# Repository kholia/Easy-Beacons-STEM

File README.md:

### Easy Beacons

A simple and easy Raspberry Pi Pico powered WSPR, and FT8 beacon system which
uses GPS for timing.

Note: The whole project can be assembled on a breadboard (including the [~100mW
amplifier](./QRPp-Amplifier-v2)) in under an hour - do give it a go!

The whole design is modular, parametric (cost and others), field repairable,
and super extensible. It is almost trivial to add support for more `beacon
modes`.

Note: This documentation is a WIP (work-in-progress), and can't be trusted
100%. Please switch on your brain, and read the actual code and schematics.
This repository has more than 10 sub-projects, and can get confusing to follow
unless you read the actual code, and schematics.

#### Build Steps

Use a stable version of the Arduino IDE 1.8.19 or later to build the project.

If you are on Linux, execute the following steps:

```
sudo apt-get install git  # install 'git' if needed

git clone https://github.com/kholia/Easy-Beacons-STEM.git

make install_arduino_cli
make install_platform
make deps
```

If you are using Windows OS, execute the following steps:

- Download this repository.

- Extract the downloaded zip file to a folder.

- Run the `setup_arduino_ide.bat` file inside this folder.

Note: Change the following lines in the code to use your values:

```
char message[] = "VU3CER VU3FOE MK68";
char call[] = "VU3FOE";
char loc[] = "MK68";
uint8_t dbm = 27;
```

#### Amplified-WSPR-Beacon-v3

- Power from a USB power bank @ 5v.

Note: The PCB version of the `Amplified-WSPR-Beacon-v3` sub-project uses the
`Pico-Beacons-GPS-v2` firmware (code).

#### Amplified-WSPR-Beacon

- Do NOT power with more than 8.4v!

- Use an 7.5v AC adapter for continuous use

Note: The PCB version of the `Amplified-WSPR-Beacon` sub-project uses the `Pico-Beacons-GPS-v2` firmware (code).

Note 2: The `Amplified-WSPR-Beacon-v2` project uses 5v from USB.

#### Usage

When `SW1` switch is OFF, the system acts as a WSPR beacon.

When `SW1` switch is ON, the system acts as a FT8 beacon.

TIP: Please use a local (or nearby) receiver to receive and decode the beacon
signals! This is important to ensure that your beacon is TX'ing correctly.

#### Schematic

Here is the schematic for the `Pico-Beacons` sketch:

Pin 16 (GP16) is SDA and Pin 17 (GP17) is SCL - connect Si5351 module to these
pins. Connect GPS's TX pin to pin 12 (GP9) of Pi Pico.

#### Performance

7W (or less) of HF RF power offers global communications coverage when
propagation is good:

WSPR mode demo:

#### Battery System Recommendation

I recommend using a LiFePo4 (LFP) battery which has good energy density and is
also priced decently well.

Use the LFP battery with a `1S LFP BMS`.

The BMS' output can be connected directly to the 3.3v input of the ESP8266
module.

https://www.waveshare.com/wiki/Solar_Power_Manager - this `Solar Power
Management Module, for 6V~24V Solar Panel` works pretty well.

#### Power Notes

This will need a HF RF PA in many cases to be usable on the air.

You can also start with the easy-to-build and breadboard-friendly [QRPp-Amplifier-v2](./QRPp-Amplifier-v2).

#### Safety Notes

- Connect a 1k or 2.2k resistor between Si5351 CLK outputs and GND.

- Connect a series 100nF at Si5351 CLK outputs.

- Do NOT connect a LED to the output(s) of Si5351 directly. Use a 330 or 470
  ohm resistor in series or use a transistor driver at the Si5351 outputs
  (better).

#### Compliance Notes

Please use a LPF at the output.

#### Gotchas

- https://github.com/mikalhart/TinyGPSPlus/issues/30 (NEO-6M modules can be buggy)

#### BOM

- 1 x 3/5mm LED (purple or pink is recommended)

- 1 x small regular (spst) chassis mount switch

- 1 x 0.25w 470 ohm resistor (CFR / MFR)

- High quality dupont cables / jumper cables

- Couple of 100nF 50V MLCC

- Zero PCB of a suitable size

- Raspberry Pi Pico board

- GPS module - NEO-7-M or better

- BS170 MOSFET (original only)

- SN74ACT00N (DIP 14 NAND Logic IC)

- Si5351A Module

#### Install the firmware on Pi Pico

- Hold down the BOOTSEL button on your Pico (keep holding it down) and plug it
  into your computer's USB port.

  Now release the BOOTSEL button.

- Open Explorer, and open the RPI-RP2 directory like you would any other hard
  drive.

- Drag and drop the UF2 file (`firmware.uf2`) from this folder into the RPI-RP2
  directory.

- Done ;)

#### Build from source

Use the latest Arduino IDE along with https://github.com/earlephilhower/arduino-pico
to build this source code.

#### Next Steps

Check out the ADX and PDX radio designs for added fun!

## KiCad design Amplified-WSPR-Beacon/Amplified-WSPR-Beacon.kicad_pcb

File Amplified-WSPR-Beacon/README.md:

Output with 7.4v @ drain is around 400mW @ 28 MHz. Not too bad - twice that of
the `Intl. WSPR Beacon` device.

This project is also called the `Rogue Radio - v1` ;)

Cost: < 1800 INR (not including the 2s 18650 battery pack) which is around 22
USD.

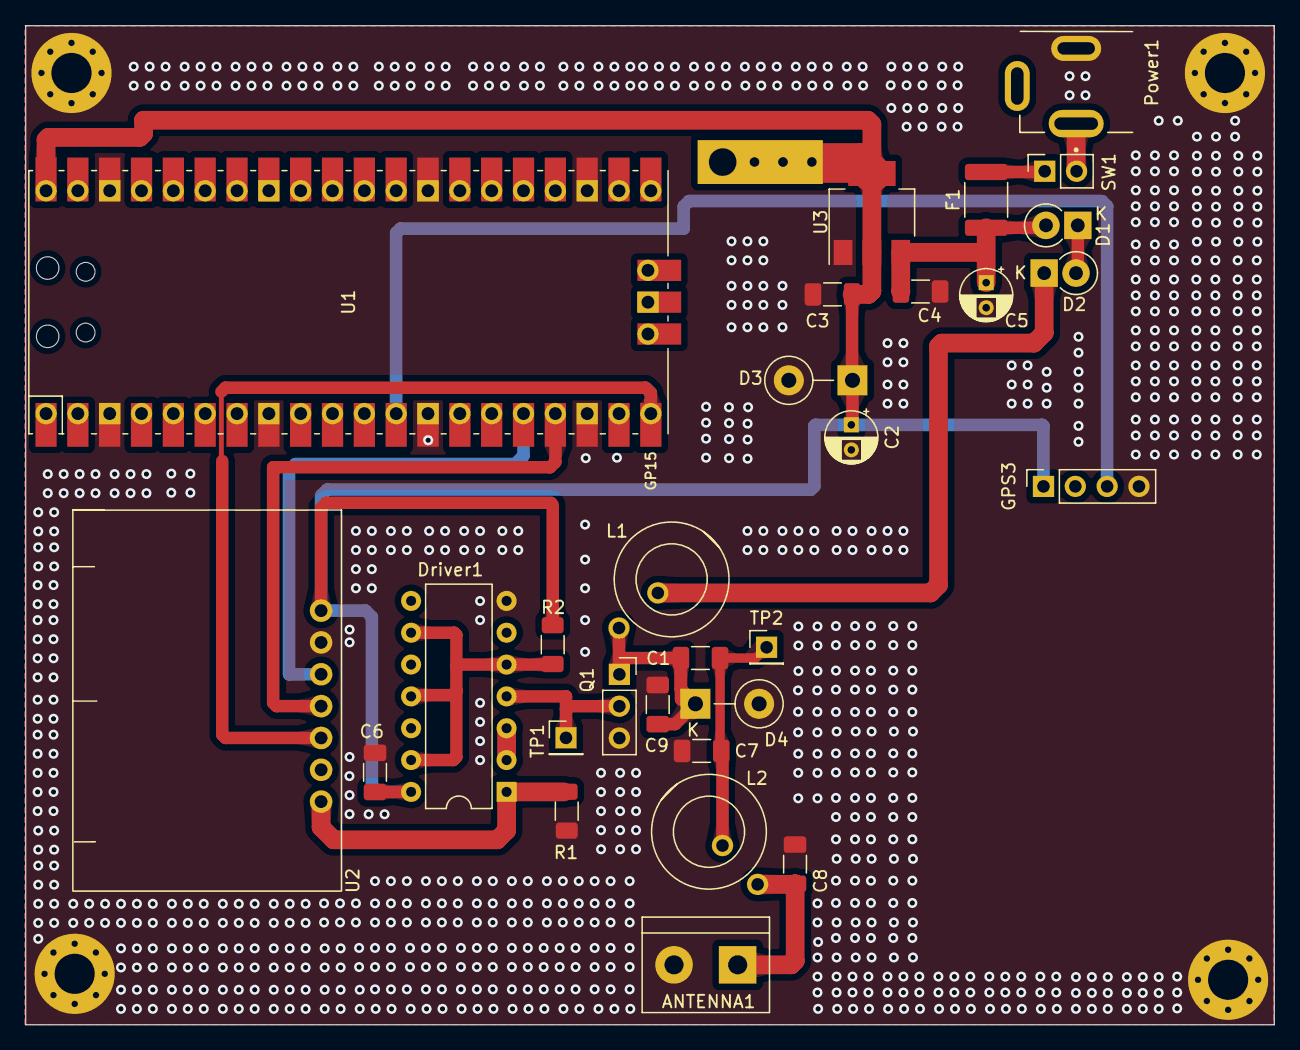
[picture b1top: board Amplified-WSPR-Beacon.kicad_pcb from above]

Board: 2 copper layers, 99.6 x 79.7 mm, 34 parts (0 on the bottom side), 18 nets.

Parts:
ANTENNA1: Screw_Terminal_01x02; TerminalBlock_bornier-2_P5.08mm
C1, C3, C4, C6: 100nF; C_1206_3216Metric_Pad1.33x1.80mm_HandSolder
C2: 10uF/16V; CP_Radial_D4.0mm_P2.00mm
C5: 100uF/16V; CP_Radial_D4.0mm_P2.00mm
C7, C8: 220p; C_1206_3216Metric_Pad1.33x1.80mm_HandSolder
C9: 100pF; C_1206_3216Metric_Pad1.33x1.80mm_HandSolder
D1, D2: 1N4007; D_DO-41_SOD81_P2.54mm_Vertical_KathodeUp
D3: 5.6V 5W; D_DO-15_P5.08mm_Vertical_KathodeUp
D4: 47v 5W; D_DO-15_P5.08mm_Vertical_KathodeUp
Driver1: SN74ACT04N; DIP-14_W7.62mm
F1: 1A (PPTC); Fuse_1812_4532Metric_Pad1.30x3.40mm_HandSolder
GPS3: GY-NEO6MV2-Module; PinSocket_1x04_P2.54mm_Vertical
H1, H2, H3, H4: MountingHole; MountingHole_3.2mm_M3_Pad_Via
HS1: Heatsink_Pad; ThermalPad_Final
L1: L; FT37-INDUCTOR
L2: 260nH (T50-2, ~8 turns); FT37-INDUCTOR
Power1: DC-005 (Barrel Jack); XKB_DC-005-5A-2.0_Modded
Q1: BS170; PinSocket_1x03_P2.54mm_Vertical
R1, R2: 2.2k; R_1206_3216Metric_Pad1.30x1.75mm_HandSolder
SW1: Jumper_2_Open; PinSocket_1x02_P2.54mm_Vertical
TP1, TP2: TestPoint; PinHeader_1x01_P2.54mm_Vertical
U1: Pico; RPi_Pico_SMD_TH
U2: SI5351-Module-VFO; SI5351 Module
U3: NCP1117-5.0; SOT-223-3_TabPin2

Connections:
+5V: C2.1, C3.1, C6.1, D3.1 (K), Driver1.14 (VCC), GPS3.1 (VCC), HS1.1, R2.2, U1.40 (VBUS), U2.1 (VIN), U3.2 (VO)
+VDC: D2.1 (K), L1.1
GND: ANTENNA1.2, C2.2, C3.2, C4.2, C5.2, C6.2, C7.2, C8.2, C9.2, D3.2 (A), D4.2 (A), Driver1.7 (GND), GPS3.4 (GND), H1.1, H2.1, H3.1, H4.1, Power1.2, Q1.3 (S), R1.2, U1.3 (GND), U1.8 (GND), U1.13 (GND), U1.18 (GND), U1.23 (GND), U1.28 (GND), U1.38 (GND), U2.2 (GND), U3.1 (GND)
unnamed: ANTENNA1.1, C8.1, L2.2
unnamed: C1.1, C7.1, L2.1, TP2.1
unnamed: C4.1, C5.1, D1.2 (A), F1.1, U3.3 (VI)
unnamed: D1.1 (K), D2.2 (A)
unnamed: C1.2, C9.1, D4.1 (K), L1.2, Q1.1 (D)
unnamed: Driver1.1 (1A), R1.1, U2.7 (SO)
unnamed: Driver1.2 (1Y), Driver1.3 (2A)
unnamed: Driver1.4 (2Y), Q1.2 (G), TP1.1
unnamed: Driver1.5 (3A), Driver1.9 (4A), Driver1.11 (5A), Driver1.13 (6A), R2.1
unnamed: GPS3.3 (TX), U1.12 (GPIO9)
unnamed: F1.2, SW1.1 (A)
unnamed: Power1.1, SW1.2 (B)
unnamed: U1.16 (GPIO12), U2.3 (SDA)
unnamed: U1.17 (GPIO13), U2.4 (SCL)
unnamed: U1.20 (GPIO15), U2.5 (S2)

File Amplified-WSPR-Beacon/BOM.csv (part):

Source:,Easy-Beacons-STEM/Amplified-WSPR-Beacon/Amplified-WSPR-Beacon.kicad_sch,,,,,,,
Date:,Sun 20 Nov 2022 02:35:45 PM IST,,,,,,,
Tool:,Eeschema 6.0.9-8da3e8f707~116~ubuntu22.04.1,,,,,,,
Generator:,/usr/share/kicad/plugins/bom_csv_grouped_by_value.py,,,,,,,
Component Count:,33,,,,,,,
,,,,,,,,
Individual Components:,,,,,,,,
,,,,,,,,
Item,Qty,Reference(s),Value,LibPart,Footprint,Datasheet,Populate,URL
,,ANTENNA1,Screw_Terminal_01x02,Connector:Screw_Terminal_01x02,TerminalBlock:TerminalBlock_bornier-2_P5.08mm,~,no,https://www.digikey.com/en/products/detail/weidm%C3%BCller/1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
,,C1,100nF,Device:C,Capacitor_SMD:C_1206_3216Metric_Pad1.33x1.80mm_HandSolder,~,yes,https://www.digikey.com/en/products/detail/yageo/CC1206KRX7R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
,,C2,10uF/16V,Device:C_Polarized,Capacitor_THT:CP_Radial_D4.0mm_P2.00mm,~,no,https://www.digikey.com/en/products/detail/nichicon/UVR1C100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
,,C3,100nF,Device:C,Capacitor_SMD:C_1206_3216Metric_Pad1.33x1.80mm_HandSolder,~,yes,https://www.digikey.com/en/products/detail/yageo/CC1206KRX7R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
,,C4,100nF,Device:C,Capacitor_SMD:C_1206_3216Metric_Pad1.33x1.80mm_HandSolder,~,yes,https://www.digikey.com/en/products/detail/yageo/CC1206KRX7R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
,,C5,100uF/16V,Device:C_Polarized,Capacitor_THT:CP_Radial_D4.0mm_P2.00mm,~,no,https://www.digikey.com/en/products/detail/rubycon/16YXF100M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
,,C6,100nF,Device:C_Small,Capacitor_SMD:C_1206_3216Metric_Pad1.33x1.80mm_HandSolder,~,yes,https://www.digikey.com/en/products/detail/yageo/CC1206KRX7R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
,,C7,220p,Device:C_Small,Capacitor_SMD:C_1206_3216Metric_Pad1.33x1.80mm_HandSolder,~,yes,https://www.digikey.com/en/products/detail/yageo/CC1206JRNPO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
,,C8,220p,Device:C_Small,Capacitor_SMD:C_1206_3216Metric_Pad1.33x1.80mm_HandSolder,~,yes,https://www.digikey.com/en/products/detail/yageo/CC1206JRNPO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
,,D1,1N4007,Diode:1N4007,Diode_THT:D_DO-41_SOD81_P2.54mm_Vertical_KathodeUp,http://www.vishay.com/docs/88503/1n4001.pdf,no,https://www.digikey.com/en/products/detail/diodes-incorporat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
,,D2,1N4007,Diode:1N4007,Diode_THT:D_DO-41_SOD81_P2.54mm_Vertical_KathodeUp,http://www.vishay.com/docs/88503/1n4001.pdf,no,https://www.digikey.com/en/products/detail/diodes-incorporat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
,,D3,5.6V 5W,Device:D_Zener,Diode_THT:D_DO-15_P5.08mm_Vertical_KathodeUp,~,no,https://www.digikey.com/en/products/detail/onsemi/1N5339BRLG/822783
,,D4,47v 5W,Device:D_Zener,Diode_THT:D_DO-15_P5.08mm_Vertical_KathodeUp,~,no,https://www.digikey.in/en/products/detail/onsemi/1N5368BG/13476793
,,Driver1,SN74ACT04N,SN74HC04N:SN74HC04N,Package_DIP:DIP-14_W7.62mm,,no,https://www.digikey.com/en/products/detail/texas-instruments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
,,F1,1A (PPTC),Device:Polyfuse_Small,Fuse:Fuse_1812_4532Metric_Pad1.30x3.40mm_HandSolder,~,yes,https://www.digikey.com/en/products/detail/bourns-inc/MF-MSM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
,,GPS3,GY-NEO6MV2-Module,GPS-Module:GPS-Module,Connector_PinSocket_2.54mm:PinSocket_1x04_P2.54mm_Vertical,,no,https://quartzcomponents.com/products/neo6mv2-gps-module-wit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
,,H1,MountingHole,Mechanical:MountingHole,MountingHole:MountingHole_3.2mm_M3,~,no,N/A
,,H2,MountingHole,Mechanical:MountingHole,MountingHole:MountingHole_3.2mm_M3,~,no,N/A
,,H3,MountingHole,Mechanical:MountingHole,MountingHole:MountingHole_3.2mm_M3,~,no,N/A
,,H4,MountingHole,Mechanical:MountingHole,MountingHole:MountingHole_3.2mm_M3,~,no,N/A
,,HS1,Heatsink_Pad,Mechanical:Heatsink_Pad,footprints:ThermalPad_Final,~,no,N/A
,,L1,L,Device:L,footprints:FT37-INDUCTOR,FT37-43,no,https://kitsandparts.com/
,,L2,"260nH (T50-2, ~8 turns)",Device:L,footprints:FT37-INDUCTOR,FT50-2,no,https://kitsandparts.com/
,,Power1,DC-005 (Barrel Jack),Connector:Barrel_Jack_Switch,footprints:XKB_DC-005-5A-2.0_Modded,~,no,https://www.lcsc.com/product-detail/Power-Connectors_XKB-Ent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
,,Q1,BS170,Transistor_FET:BS170,Connector_PinSocket_2.54mm:PinSocket_1x03_P2.54mm_Vertical,https://www.onsemi.com/pub/Collateral/BS170-D.PDF,no,https://www.tme.eu/en/details/bs170/tht-n-channel-transistor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
,,R1,2.2k,Device:R_Small,Resistor_SMD:R_1206_3216Metric_Pad1.30x1.75mm_HandSolder,~,yes,https://www.digikey.com/en/products/detail/yageo/RT1206FRE07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
,,R2,2.2k,Device:R_Small,Resistor_SMD:R_1206_3216Metric_Pad1.30x1.75mm_HandSolder,~,yes,https://www.digikey.com/en/products/detail/yageo/RT1206FRE07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
,,SW1,Jumper_2_Open,Jumper:Jumper_2_Open,Connector_PinSocket_2.54mm:PinSocket_1x02_P2.54mm_Vertical,~,no,https://www.digikey.com/en/products/detail/sullins-connector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
,,TP1,TestPoint,Connector:TestPoint,Connector_PinHeader_2.54mm:PinHeader_1x01_P2.54mm_Vertical,~,no,https://robu.in/product/1x40-berg-strip-male-connector/
,,TP2,TestPoint,Connector:TestPoint,Connector_PinHeader_2.54mm:PinHeader_1x01_P2.54mm_Vertical,~,no,https://robu.in/product/1x40-berg-strip-male-connector/
,,U1,Pico,pico_fixed:Pico,footprints:RPi_Pico_SMD_TH,,no,https://www.digikey.com/en/products/detail/raspberry-pi/SC09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
,,U2,SI5351-Module-VFO,Control-Board-rescue:SI5351Module_2-VFO-SDR_SSB-rescue-Hack-v1-rescue,footprints:SI5351 Module,,no,https://www.adafruit.com/product/2045
,,U3,NCP1117-5.0,Regulator_Linear:AMS1117-5.0,Package_TO_SOT_SMD:SOT-223-3_TabPin2,http://www.advanced-monolithic.com/pdf/ds1117.pdf,yes,https://www.tme.com/in/en/details/ncp1117st50t3g/ldo-unregul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
,,,,,,,,
,,,,,,,,
,,,,,,,,
Collated Components:,,,,,,,,
,,,,,,,,
Item,Qty,Reference(s),Value,LibPart,Footprint,Datasheet,Populate,URL
1,1,ANTENNA1,Screw_Terminal_01x02,Connector:Screw_Terminal_01x02,TerminalBlock:TerminalBlock_bornier-2_P5.08mm,~,no,https://www.digikey.com/en/products/detail/weidm%C3%BCller/1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
2,3,"C1, C3, C4",100nF,Device:C,Capacitor_SMD:C_1206_3216Metric_Pad1.33x1.80mm_HandSolder,~,yes,https://www.digikey.com/en/products/detail/yageo/CC1206KRX7R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
3,1,C2,10uF/16V,Device:C_Polarized,Capacitor_THT:CP_Radial_D4.0mm_P2.00mm,~,no,https://www.digikey.com/en/products/detail/nichicon/UVR1C100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
4,1,C5,100uF/16V,Device:C_Polarized,Capacitor_THT:CP_Radial_D4.0mm_P2.00mm,~,no,https://www.digikey.com/en/products/detail/rubycon/16YXF100M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
5,1,C6,100nF,Device:C_Small,Capacitor_SMD:C_1206_3216Metric_Pad1.33x1.80mm_HandSolder,~,yes,https://www.digikey.com/en/products/detail/yageo/CC1206KRX7R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
6,2,"C7, C8",220p,Device:C_Small,Capacitor_SMD:C_1206_3216Metric_Pad1.33x1.80mm_HandSolder,~,yes,https://www.digikey.com/en/products/detail/yageo/CC1206JRNPO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
7,2,"D1, D2",1N4007,Diode:1N4007,Diode_THT:D_DO-41_SOD81_P2.54mm_Vertical_KathodeUp,http://www.vishay.com/docs/88503/1n4001.pdf,no,https://www.digikey.com/en/products/detail/diodes-incorporat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
8,1,D3,5.6V 5W,Device:D_Zener,Diode_THT:D_DO-15_P5.08mm_Vertical_KathodeUp,~,no,https://www.digikey.com/en/products/detail/onsemi/1N5339BRLG/822783
9,1,D4,47v 5W,Device:D_Zener,Diode_THT:D_DO-15_P5.08mm_Vertical_KathodeUp,~,no,https://www.digikey.in/en/products/detail/onsemi/1N5368BG/13476793
10,1,Driver1,SN74ACT04N,SN74HC04N:SN74HC04N,Package_DIP:DIP-14_W7.62mm,,no,https://www.digikey.com/en/products/detail/texas-instruments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
11,1,F1,1A (PPTC),Device:Polyfuse_Small,Fuse:Fuse_1812_4532Metric_Pad1.30x3.40mm_HandSolder,~,yes,https://www.digikey.com/en/products/detail/bourns-inc/MF-MSM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
12,1,GPS3,GY-NEO6MV2-Module,GPS-Module:GPS-Module,Connector_PinSocket_2.54mm:PinSocket_1x04_P2.54mm_Vertical,,no,https://quartzcomponents.com/products/neo6mv2-gps-module-wit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
13,4,"H1, H2, H3, H4",MountingHole,Mechanical:MountingHole,MountingHole:MountingHole_3.2mm_M3,~,no,N/A
14,1,HS1,Heatsink_Pad,Mechanical:Heatsink_Pad,footprints:ThermalPad_Final,~,no,N/A
15,1,L1,L,Device:L,footprints:FT37-INDUCTOR,FT37-43,no,https://kitsandparts.com/
16,1,L2,"260nH (T50-2, ~8 turns)",Device:L,footprints:FT37-INDUCTOR,FT50-2,no,https://kitsandparts.com/
17,1,Power1,DC-005 (Barrel Jack),Connector:Barrel_Jack_Switch,footprints:XKB_DC-005-5A-2.0_Modded,~,no,https://www.lcsc.com/product-detail/Power-Connectors_XKB-Ent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
18,1,Q1,BS170,Transistor_FET:BS170,Connector_PinSocket_2.54mm:PinSocket_1x03_P2.54mm_Vertical,https://www.onsemi.com/pub/Collateral/BS170-D.PDF,no,https://www.tme.eu/en/details/bs170/tht-n-channel-transistor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

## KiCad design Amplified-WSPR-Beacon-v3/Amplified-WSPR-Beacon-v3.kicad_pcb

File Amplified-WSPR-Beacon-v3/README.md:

### Easy Beacons

A simple and easy Raspberry Pi Pico W powered WSPR, and FT8 beacon system which
uses RTC (DS3231) for timing.

The whole design is modular, parametric (cost and others), field repairable,
and super extensible. It is almost trivial to add support for more `beacon
modes`.

Cost to build: Less than 2300 INR (< 28 USD).

Cost breakdown: PCB (175) + Si5351 module (479) + Pico W (649) + Octal Driver
chip (85) + Passives (50) + Connectors (25) + Toroids (40) + RTC module (275) +
Wire (30) + Wire Ferrules (10) + Misc (50) + 425 (TR1).

Power output: 250mW even @ 28 MHz with a 5v supply (via USB).

Note: The kit needs to be (soldering) friendly enough - it will be built by
senior folks as well as young kids.

[UPDATE] This PCB was validated on 24-Feb-2023 - everything works great!

#### Build Steps

Use a stable version of the Arduino IDE 1.8.19 or later to build the project.

If you are on Linux, execute the following steps:

```
sudo apt-get install git  # install 'git' if needed

git clone https://github.com/kholia/Easy-Beacons-STEM.git

make install_arduino_cli
make install_platform
make deps
```

If you are using Windows OS, execute the following steps:

- Download this repository.

- Extract the downloaded zip file to a folder.

- Run the `setup_arduino_ide.bat` file inside this folder.

Note: Change the following lines in the code to use your own values:

```
char call[] = "VU3CER";
char loc[] = "MK68";
uint8_t dbm = 23;
```

#### Amplified-WSPR-Beacon-v3

- Supply 5v to Raspberry Pico W using a mobile (phone) charger or a USB 5v
  battery bank.

Note: The PCB version of the `Amplified-WSPR-Beacon-v3` sub-project uses the
code from the `firmware` folder.

#### Usage

TIP: Please use a local (or nearby) receiver to receive and decode the beacon
signals! This is important to ensure that your beacon is calibrated and TX'ing
correctly.

#### Safety Notes

- Connect a 1k or 2.2k resistor between Si5351 CLK outputs and GND.

- Connect a series 100nF at Si5351 CLK outputs.

- Do NOT connect a LED to the output(s) of Si5351 directly for educational
  purposes. Use a 330 or 470 ohm resistor in series or use a transistor driver
  at the Si5351 outputs (much better).

#### BOM

- 1 x 3/5mm LED (purple or pink is recommended)

- 1 x 0.25W 2.2k ohms CFR / MFR (resistor)

- Couple of 100nF 50V MLCC caps

- 100uF/16V electrolytic caps

- 220pF C0G MLCC caps

- 27 to 29 SWG copper winding ("magnetic") wire

  - PTFE (teflon) winding wire could be better

- PCB Terminal Block (5.08mm spacing, 2 holes)

- Raspberry Pi Pico W board

- DS3231 RTC module

- SN74ACT244N (Fast DIP-20 Octal Driver)

- T2-613-1 IC (1:1:2 transformer IC from Mini-Circuits)

- Si5351A Module (with TCXO preferably)

#### Install the firmware on Pi Pico

- Hold down the BOOTSEL button on your Pico (keep holding it down) and plug it
  into your computer's USB port.

  Now release the BOOTSEL button.

- Open Explorer, and open the RPI-RP2 directory like you would any other hard
  drive.

- Drag and drop the UF2 file (`firmware.uf2`) from this folder into the RPI-RP2
  directory.

- Done ;)

#### Build from source

Use the latest Arduino IDE along with https://github.com/earlephilhower/arduino-pico
to build this source code.

#### Next Steps

Check out the "DDX - Direct Digital Transceiver" design for added fun!

#### Tips

- https://en.wikipedia.org/wiki/Electric_wire_ferrule - Use wire ferrules for the antenna wires

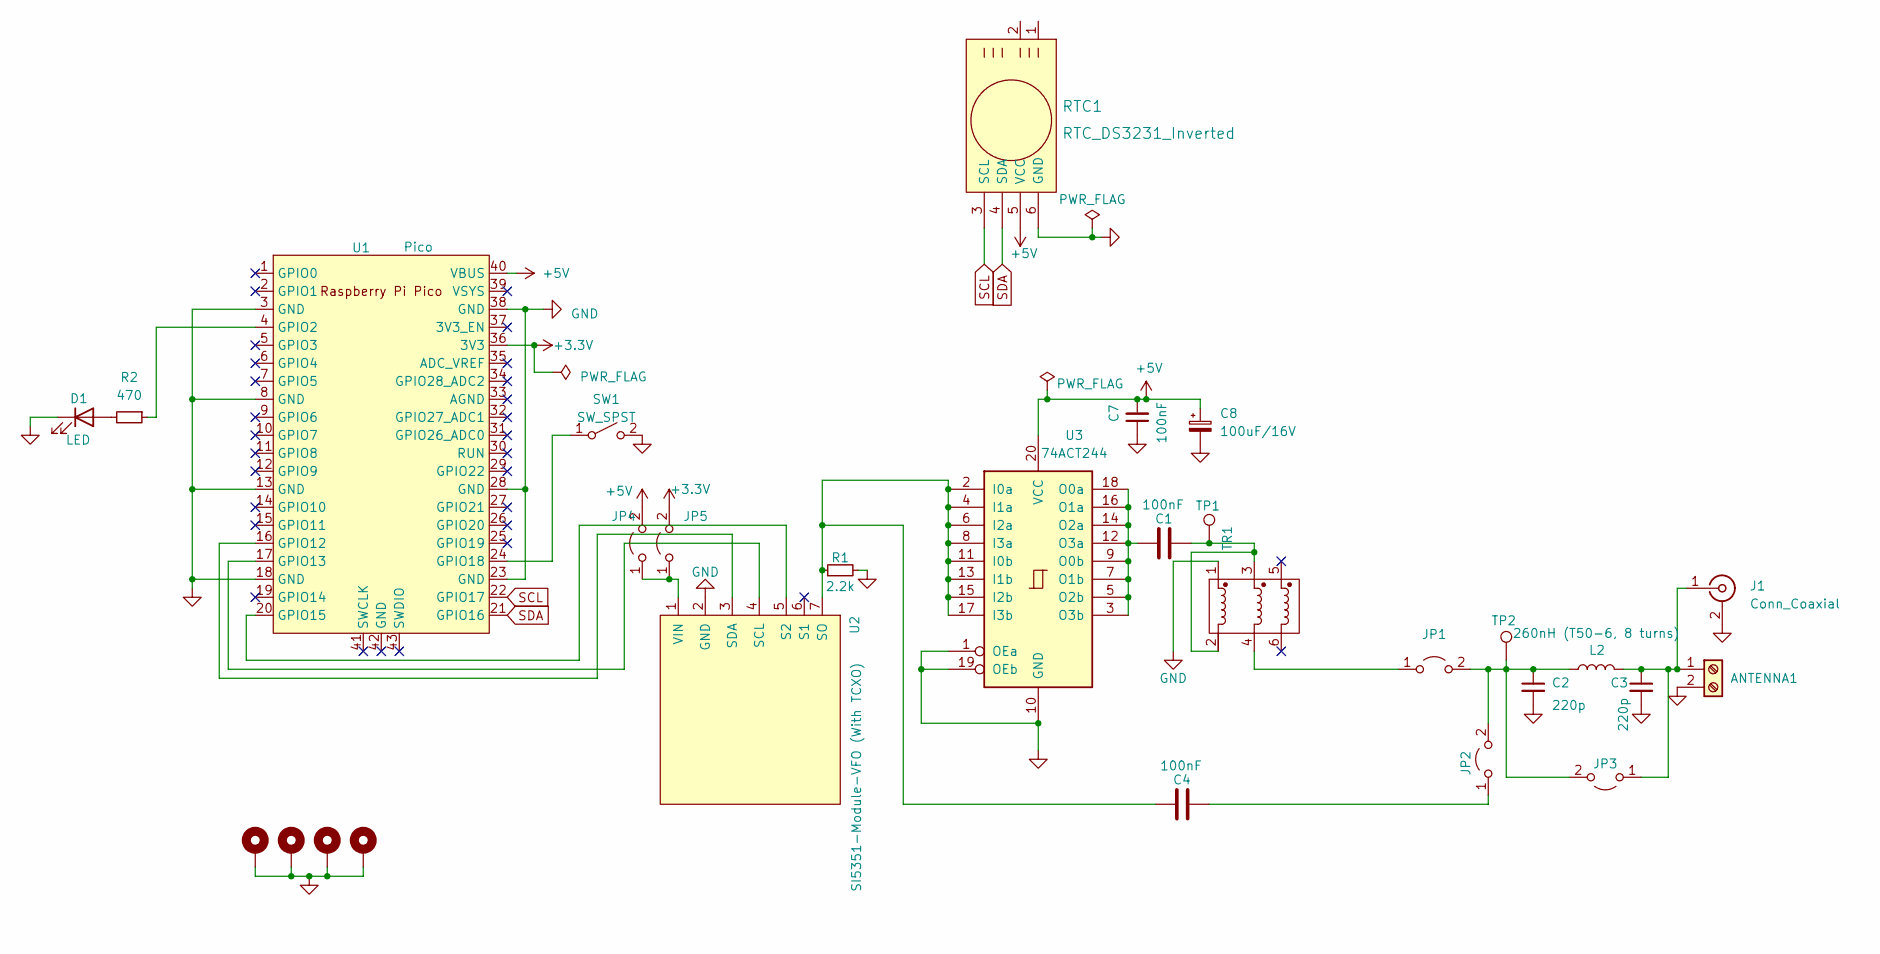
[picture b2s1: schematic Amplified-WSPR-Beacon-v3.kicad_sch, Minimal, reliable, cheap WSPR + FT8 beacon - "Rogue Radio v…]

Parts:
ANTENNA1: Screw_Terminal_01x02; TerminalBlock_bornier-2_P5.08mm
C1, C4, C7: 100nF; C_Disc_D3.0mm_W1.6mm_P2.50mm
C2, C3: 220p; C_Disc_D3.0mm_W1.6mm_P2.50mm
C8: 100uF/16V; CP_Radial_D4.0mm_P2.00mm
D1: LED; LED_D3.0mm
H1, H2, H3, H4: MountingHole_Pad; MountingHole_3.2mm_M3_Pad_Via
J1: Conn_Coaxial; SMA_Samtec_SMA-J-P-X-ST-EM1_EdgeMount
JP1, JP2, JP3, JP4, JP5: Jumper_2_Open; SolderJumper-2_P1.3mm_Open_TrianglePad1.0x1.5mm
L2: 260nH (T50-6, 8 turns); T37-2
R1: 2.2k; R_Axial_DIN0204_L3.6mm_D1.6mm_P1.90mm_Vertical
R2: 470; R_Axial_DIN0204_L3.6mm_D1.6mm_P1.90mm_Vertical
RTC1: RTC_DS3231_Inverted; PinSocket_1x06_P2.54mm_Horizontal
SW1: SW_SPST; PinSocket_1x02_P2.54mm_Vertical
TP1, TP2: TestPoint; PinHeader_1x01_P2.54mm_Vertical
TR1: T2-613-1+; KK81
U1: Pico; RPi_Pico_SMD_TH
U2: SI5351-Module-VFO (With TCXO); SI5351 Module
U3: 74ACT244; DIP-20_W7.62mm_LongPads

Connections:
+3.3V: JP5.2 (B), U1.36 (3V3)
+5V: C7.2, C8.1, JP4.2 (B), RTC1.5 (VCC), U1.40 (VBUS), U3.20 (VCC)
unnamed: ANTENNA1.1, C3.1, J1.1 (In), JP3.1 (A), L2.2
unnamed: C1.1, TP1.1, TR1.2, TR1.3
unnamed: D1.2 (A), R2.2
unnamed: JP1.1 (A), TR1.4
unnamed: C2.1, JP1.2 (B), JP2.2 (B), JP3.2 (B), L2.1, TP2.1
unnamed: C4.1, JP2.1 (A)
unnamed: JP4.1 (A), JP5.1 (A), U2.1 (VIN)
unnamed: SW1.1 (A), U1.24 (GPIO18)
unnamed: R2.1, U1.4 (GPIO2)
unnamed: U1.16 (GPIO12), U2.3 (SDA)
unnamed: U1.17 (GPIO13), U2.4 (SCL)
unnamed: U1.20 (GPIO15), U2.5 (S2)
unnamed: C4.2, R1.1, U2.7 (SO), U3.2 (I0a), U3.4 (I1a), U3.6 (I2a), U3.8 (I3a), U3.11 (I0b), U3.13 (I1b), U3.15 (I2b), U3.17 (I3b)
unnamed: C1.2, U3.3 (O3b), U3.5 (O2b), U3.7 (O1b), U3.9 (O0b), U3.12 (O3a), U3.14 (O2a), U3.16 (O1a), U3.18 (O0a)
SCL: RTC1.3 (SCL), U1.22 (GPIO17)
SDA: RTC1.4 (SDA), U1.21 (GPIO16)

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
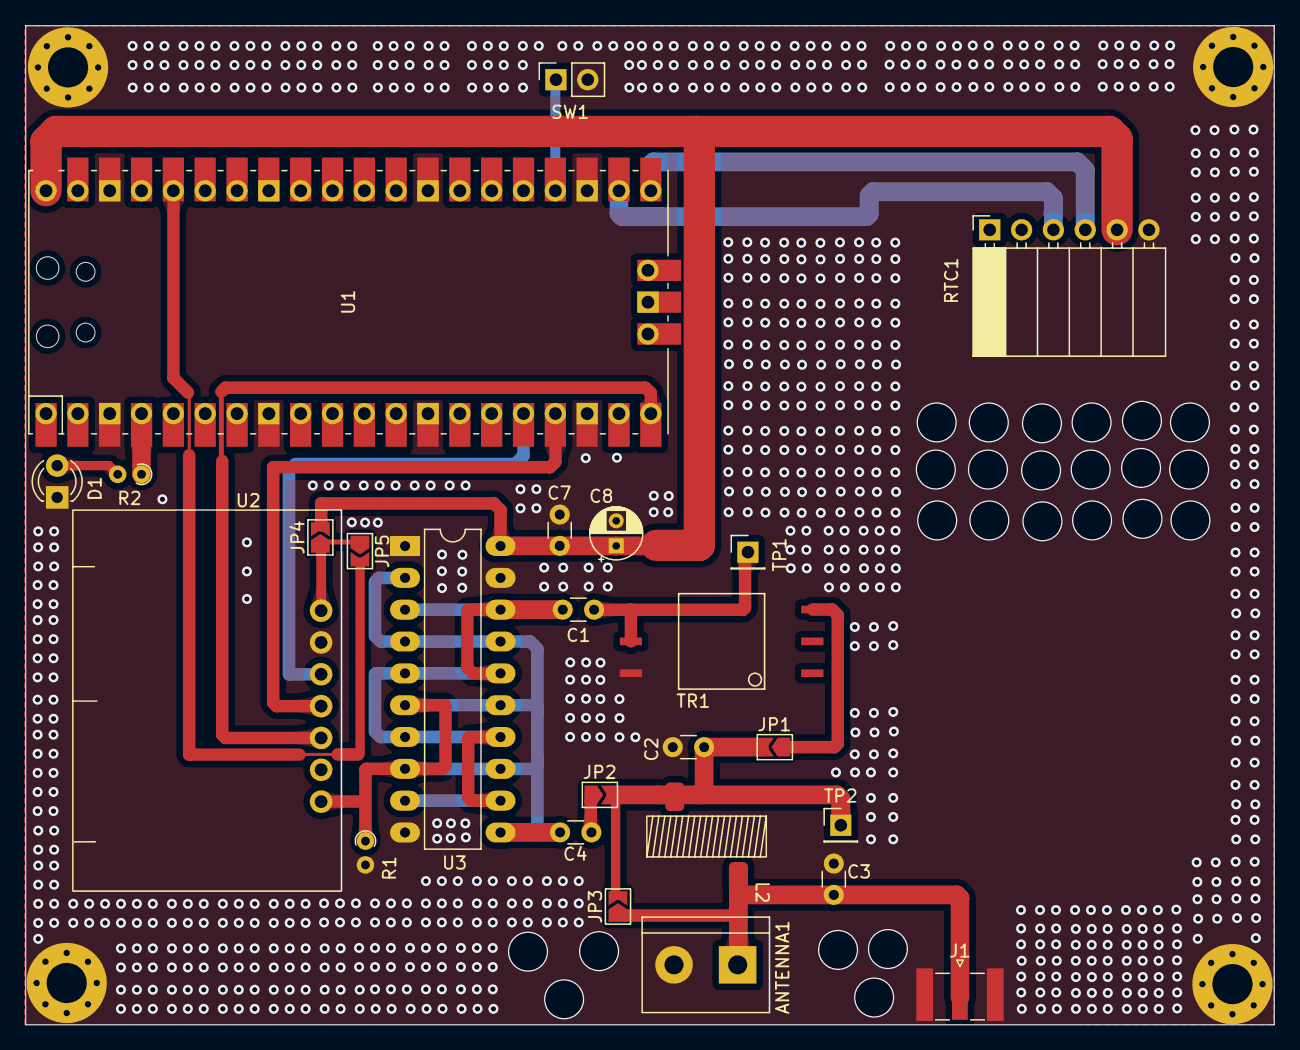
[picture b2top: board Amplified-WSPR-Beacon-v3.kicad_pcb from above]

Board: 2 copper layers, 99.6 x 79.7 mm, 29 parts (0 on the bottom side), 19 nets.

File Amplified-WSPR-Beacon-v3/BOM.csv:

"Reference","Value","Footprint","Datasheet","Populate","URL","Qty"
"ANTENNA1","Screw_Terminal_01x02","TerminalBlock:TerminalBlock_bornier-2_P5.08mm","~","no","https://www.digikey.com/en/products/detail/weidm%C3%BCller/1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","1"
"C1, C4, C7","100nF","Capacitor_THT:C_Disc_D3.0mm_W1.6mm_P2.50mm","~","no","https://www.digikey.com/en/products/detail/vishay-beyschlag-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","3"
"C2, C3","220p","Capacitor_THT:C_Disc_D3.0mm_W1.6mm_P2.50mm","~","yes","https://www.digikey.in/en/products/detail/vishay-beyschlag-d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","2"
"C8","100uF/16V","Capacitor_THT:CP_Radial_D4.0mm_P2.00mm","~","","https://www.digikey.com/en/products/detail/rubycon/16ZLH100M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","1"
"D1","LED","Connector_PinSocket_2.54mm:PinSocket_1x02_P2.54mm_Vertical","~","","","1"
"H1-H4","MountingHole_Pad","MountingHole:MountingHole_3.2mm_M3_Pad_Via","~","","","4"
"JP1-JP3","Jumper_2_Open","Jumper:SolderJumper-2_P1.3mm_Open_TrianglePad1.0x1.5mm","~","","","3"
"L2","260nH (T50-6, ~8 turns)","footprints:T37-2","https://toroids.info/T50-6.php","no","https://kitsandparts.com/","1"
"R1","2.2k","Resistor_THT:R_Axial_DIN0204_L3.6mm_D1.6mm_P1.90mm_Vertical","~","yes","https://www.digikey.com/en/products/detail/stackpole-electro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","1"
"R2","470","Resistor_THT:R_Axial_DIN0204_L3.6mm_D1.6mm_P1.90mm_Vertical","~","","https://www.digikey.com/en/products/detail/yageo/MF0207FRE52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","1"
"RTC1","RTC_DS3231_Inverted","Connector_PinSocket_2.54mm:PinSocket_1x06_P2.54mm_Horizontal","","no","https://robu.in/product/1x40-berg-strip-right-angle-female-c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","1"
"TP1, TP2","TestPoint","Connector_PinHeader_2.54mm:PinHeader_1x01_P2.54mm_Vertical","~","no","https://robu.in/product/1x40-berg-strip-male-connector/","2"
"TR1","T2-613-1+","footprints:KK81","~","","https://www.minicircuits.com/WebStore/dashboard.html?model=T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","1"
"U1","Pico","footprints:RPi_Pico_SMD_TH","","no","https://www.digikey.com/en/products/detail/raspberry-pi/SC09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","1"
"U2","SI5351-Module-VFO (With TCXO)","footprints:SI5351 Module","","no","https://www.adafruit.com/product/2045","1"
"U3","74ACT244","Package_DIP:DIP-20_W7.62mm_LongPads","https://www.ti.com/product/SN74ACT244","no","https://www.digikey.com/en/products/detail/texas-instruments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","1"

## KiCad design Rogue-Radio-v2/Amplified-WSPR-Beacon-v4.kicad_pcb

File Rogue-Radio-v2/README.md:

### Easy Beacons

A simple and easy Raspberry Pi Pico W powered WSPR, and FT8 beacon system which
uses RTC (DS3231) for timing.

The whole design is modular, parametric (cost and others), field repairable,
and super extensible. It is almost trivial to add support for more `beacon
modes`.

Cost to build: Less than 2300 INR (< 28 USD).

Cost breakdown: PCB (175) + Si5351 module (479) + Pico W (649) + Octal Driver
chip (85) + Passives (50) + Connectors (25) + Toroids (40) + RTC module (275) +
Wire (30) + Wire Ferrules (10) + Misc (50) + 425 (TR1).

Power output: To-Be-Tested. We are expecting around 1.5W to 2W @ 28 MHz with
20v drain voltage.

Note: Heatsinking of the IRF510 is a must!

#### Build Steps

Use a stable version of the Arduino IDE 1.8.19 or later to build the project.

If you are on Linux, execute the following steps:

```
sudo apt-get install git  # install 'git' if needed

git clone https://github.com/kholia/Easy-Beacons-STEM.git

make install_arduino_cli
make install_platform
make deps
```

If you are using Windows OS, execute the following steps:

- Download this repository.

- Extract the downloaded zip file to a folder.

- Run the `setup_arduino_ide.bat` file inside this folder.

Note: Change the following lines in the code to use your own values:

```
char call[] = "VU3CER";
char loc[] = "MK68";
uint8_t dbm = 23;
```

#### Usage

TIP: Please use a local (or nearby) receiver to receive and decode the beacon
signals! This is important to ensure that your beacon is calibrated and TX'ing
correctly.

#### Safety Notes

- Connect a 1k or 2.2k resistor between Si5351 CLK outputs and GND.

- Connect a series 100nF at Si5351 CLK outputs.

- Do NOT connect a LED to the output(s) of Si5351 directly for educational
  purposes. Use a 330 or 470 ohm resistor in series or use a transistor driver
  at the Si5351 outputs (much better).

#### BOM

- 1 x 3/5mm LED (purple or pink is recommended)

- 1 x 0.25W 2.2k ohms CFR / MFR (resistor)

- Couple of 100nF 50V MLCC caps

- 100uF/16V electrolytic caps

- 220pF C0G MLCC caps

- 27 to 29 SWG copper winding ("magnetic") wire

  - PTFE (teflon) winding wire could be better

- PCB Terminal Block (5.08mm spacing, 2 holes)

- Raspberry Pi Pico W board

- DS3231 RTC module

- SN74ACT244N (Fast DIP-20 Octal Driver)

- T2-613-1 IC (1:1:2 transformer IC from Mini-Circuits)

- Si5351A Module (with TCXO preferably)

  - https://github.com/kholia/Si5351-Module-Clone-TCXO

#### Install the firmware on Pi Pico

- Hold down the BOOTSEL button on your Pico (keep holding it down) and plug it
  into your computer's USB port.

  Now release the BOOTSEL button.

- Open Explorer, and open the RPI-RP2 directory like you would any other hard
  drive.

- Drag and drop the UF2 file (`firmware.uf2`) from this folder into the RPI-RP2
  directory.

- Done ;)

#### Build from source

Use the latest Arduino IDE along with https://github.com/earlephilhower/arduino-pico
to build this source code.

#### Next Steps

Check out the "DDX - Direct Digital Transceiver" design for added fun!

#### Tips

- https://en.wikipedia.org/wiki/Electric_wire_ferrule - Use wire ferrules for the antenna wires

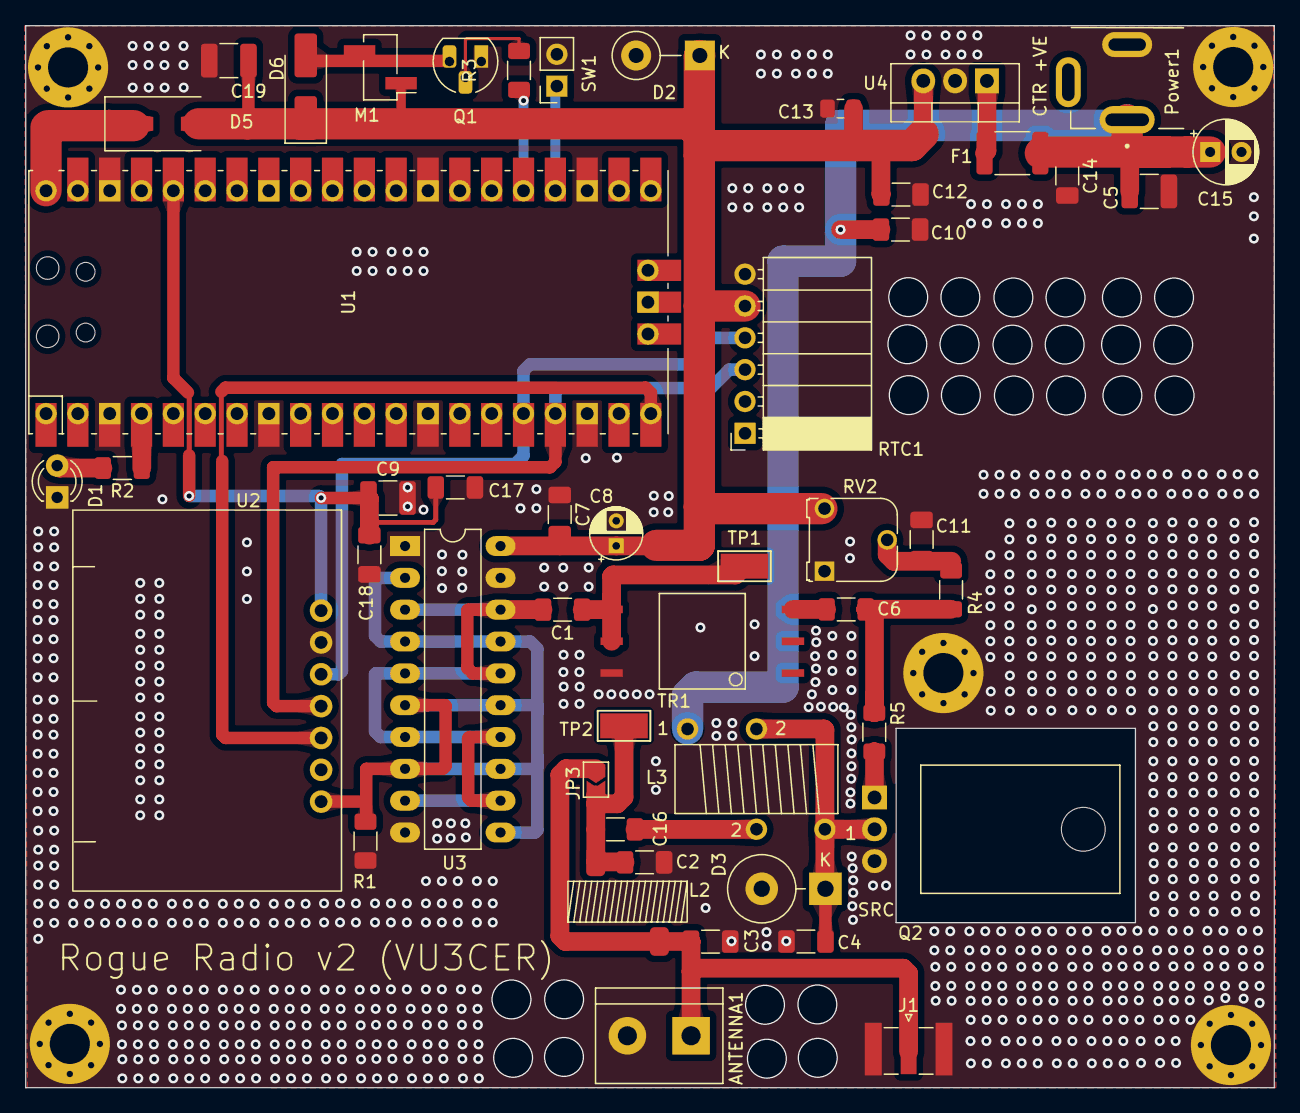
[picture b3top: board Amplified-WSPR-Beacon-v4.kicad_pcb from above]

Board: 2 copper layers, 99.6 x 84.7 mm, 54 parts (0 on the bottom side), 26 nets.

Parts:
ANTENNA1: Screw_Terminal_01x02; TerminalBlock_bornier-2_P5.08mm
C1, C6, C7, C11, C12, C14: 100nF; C_1206_3216Metric_Pad1.33x1.80mm_HandSolder
C2, C3: 220p; C_1206_3216Metric_Pad1.33x1.80mm_HandSolder
C4: 100pF; C_1206_3216Metric_Pad1.33x1.80mm_HandSolder
C5: 10uF 50v; C_1210_3225Metric_Pad1.33x2.70mm_HandSolder
C8: 100uF/16V; CP_Radial_D4.0mm_P2.00mm
C9, C19: 100u; C_1210_3225Metric_Pad1.33x2.70mm_HandSolder
C10: 10nF; C_1206_3216Metric_Pad1.33x1.80mm_HandSolder
C13: 22uF 10v; C_0805_2012Metric_Pad1.18x1.45mm_HandSolder
C15: 100uF 100v; CP_Radial_D5.0mm_P2.50mm
C16: 100nF 100v; C_1206_3216Metric_Pad1.33x1.80mm_HandSolder
C17, C18: 100n; C_1206_3216Metric_Pad1.33x1.80mm_HandSolder
D1: LED; LED_D3.0mm
D2: 5.6V 5W; D_DO-15_P5.08mm_Vertical_KathodeUp
D3: 75v 5W; D_DO-201_P5.08mm_Vertical_KathodeUp
D5: 1N5818; D_SMA-SMB_Universal_Handsoldering
D6: M7 (1N4007); D_SMA_Handsoldering
F1: 600mA; Fuse_1812_4532Metric_Pad1.30x3.40mm_HandSolder
H1, H2, H3, H4, H5: MountingHole_Pad; MountingHole_3.2mm_M3_Pad_Via
J1: Conn_Coaxial; SMA_Samtec_SMA-J-P-X-ST-EM1_EdgeMount
JP3: Jumper_2_Open; SolderJumper-2_P1.3mm_Open_TrianglePad1.0x1.5mm
L2: 260nH (T50-6, 8 turns); T37-2
L3: L_Ferrite_Coupled; FT50-43 Transformer
M1: Fan; PinHeader_1x02_P2.54mm_Vertical_SMD_Pin1Left
Power1: DC-005 (Barrel Jack); XKB_DC-005-5A-2.0_Modded
Q1: PN2222A; TO-92_HandSolder
Q2: IRF510; TO-220-3_Horizontal_TabDown
R1: 2.2k; R_1206_3216Metric_Pad1.30x1.75mm_HandSolder
R2: 470; R_1206_3216Metric_Pad1.30x1.75mm_HandSolder
R3: 1k; R_1206_3216Metric_Pad1.30x1.75mm_HandSolder
R4: 10k; R_1206_3216Metric_Pad1.30x1.75mm_HandSolder
R5: 10; R_1206_3216Metric_Pad1.30x1.75mm_HandSolder
RTC1: RTC_DS3231_Inverted; PinSocket_1x06_P2.54mm_Horizontal
RV2: 5k; Potentiometer_Runtron_RM-065_Vertical
SW1: SW_SPST; PinSocket_1x02_P2.54mm_Vertical
TP1, TP2: TestPoint; TestPoint_Keystone_5019_Minature
TR1: T2-613-1+; KK81
U1: Pico; RPi_Pico_SMD_TH
U2: SI5351-Module-VFO (With TCXO); SI5351 Module
U3: 74ACT244; DIP-20_W7.62mm_LongPads
U4: LM7805_TO220; TO-220-3_Vertical

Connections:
+3.3V: C9.1, C17.1, C18.1, U1.36 (3V3), U2.1 (VIN)
+5V: C7.2, C8.1, C12.1, C13.1, C19.1, D2.1 (K), D5.2 (A), D6.1 (K), M1.1 (+), RTC1.5 (VCC), RV2.3, U3.20 (VCC), U4.3 (VO)
+VDC: C5.1, C10.1, C14.1, C15.1, F1.2, L3.2, Power1.1
/DRAIN: C4.1, D3.1 (K), L3.1, L3.4, Q2.2 (D)
FAN: R3.1, U1.25 (GPIO19)
GND: ANTENNA1.2, C2.2, C3.2, C4.2, C5.2, C7.1, C8.2, C9.2, C10.2, C11.2, C12.2, C13.2, C14.2, C15.2, C17.2, C18.2, C19.2, D1.1 (K), D2.2 (A), D3.2 (A), H1.1, H2.1, H3.1, H4.1, H5.1, J1.2 (Ext), Power1.2, Q1.1 (E), Q2.3 (S), R1.2, RTC1.6 (GND), RV2.1, SW1.2 (B), TR1.1, U1.3 (GND), U1.8 (GND), U1.13 (GND), U1.18 (GND), U1.23 (GND), U1.28 (GND), U1.38 (GND), U2.2 (GND), U3.1 (OEa), U3.10 (GND), U3.19 (OEb), U4.2 (GND)
unnamed: ANTENNA1.1, C3.1, J1.1 (In), JP3.1 (A), L2.2
unnamed: C1.1, TP1.1, TR1.2, TR1.3
unnamed: C6.1, R4.2, R5.2
unnamed: C6.2, TR1.4
unnamed: C11.1, R4.1, RV2.2
unnamed: C16.2, L3.3
unnamed: D1.2 (A), R2.2
unnamed: D5.1 (K), U1.40 (VBUS)
unnamed: D6.2 (A), M1.2 (-), Q1.3 (C)
unnamed: C2.1, C16.1, JP3.2 (B), L2.1, TP2.1
unnamed: Q1.2 (B), R3.2
unnamed: Q2.1 (G), R5.1
unnamed: SW1.1 (A), U1.24 (GPIO18)
unnamed: R2.1, U1.4 (GPIO2)
unnamed: U1.20 (GPIO15), U2.5 (S2)
unnamed: R1.1, U2.7 (SO), U3.2 (I0a), U3.4 (I1a), U3.6 (I2a), U3.8 (I3a), U3.11 (I0b), U3.13 (I1b), U3.15 (I2b), U3.17 (I3b)
unnamed: C1.2, U3.3 (O3b), U3.5 (O2b), U3.7 (O1b), U3.9 (O0b), U3.12 (O3a), U3.14 (O2a), U3.16 (O1a), U3.18 (O0a)
unnamed: F1.1, U4.1 (VI)
SCL: RTC1.3 (SCL), U1.17 (GPIO13), U2.4 (SCL)
SDA: RTC1.4 (SDA), U1.16 (GPIO12), U2.3 (SDA)

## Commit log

2024-01-16 Introduce "Amplified-WSPR-Beacon-v3-Production" for immediate production
